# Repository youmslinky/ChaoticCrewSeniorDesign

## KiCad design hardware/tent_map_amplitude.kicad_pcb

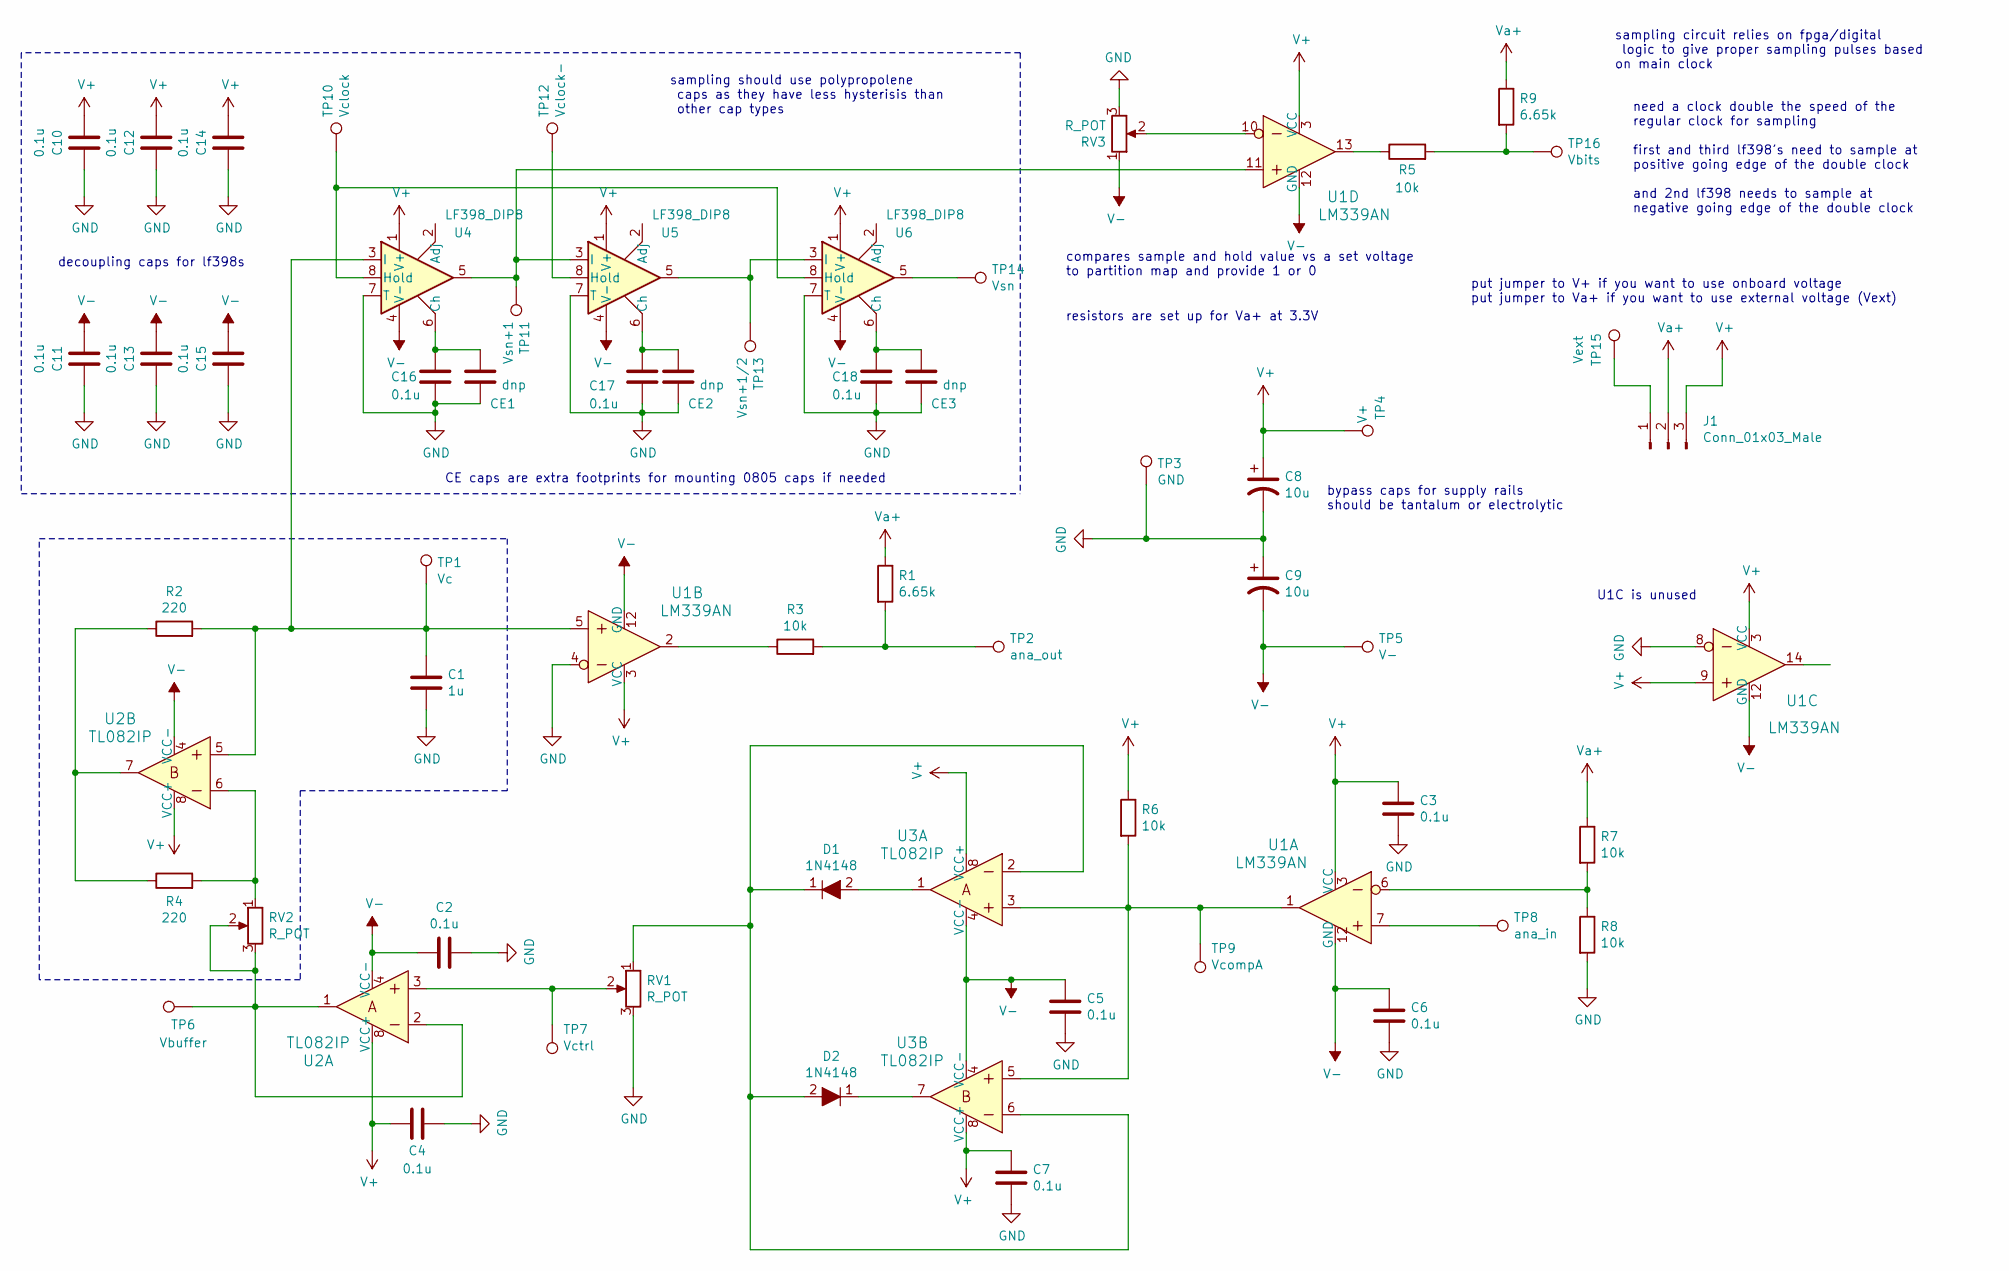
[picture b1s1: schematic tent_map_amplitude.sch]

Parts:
C1: 1u; C_0805_2012Metric_Pad1.18x1.45mm_HandSolder
C2, C3, C4, C5, C6, C7, C10, C11, C12, C13, C14, C15: 0.1u; C_0805_2012Metric_Pad1.18x1.45mm_HandSolder
C8, C9: 10u; CP_Radial_D5.0mm_P2.00mm
C16, C17, C18: 0.1u; C_Rect_L10.3mm_W5.0mm_P7.50mm_MKS4
CE1, CE2, CE3: dnp; C_0805_2012Metric_Pad1.18x1.45mm_HandSolder
D1, D2: 1N4148; Diode_DO-35_P10mm; MPN 1N4148; Digi-Key_PN 1N4148FS-ND
J1: Conn_01x03_Male; PinHeader_1x03_P2.54mm_Vertical
R1, R9: 6.65k; R_0805_2012Metric_Pad1.20x1.40mm_HandSolder
R2, R4: 220; R_0805_2012Metric_Pad1.20x1.40mm_HandSolder
R3, R5, R6, R7, R8: 10k; R_0805_2012Metric_Pad1.20x1.40mm_HandSolder
RV1, RV2, RV3: R_POT; Potentiometer_Bourns_3296W_Vertical
TP1: Vc; TestPoint_Bridge_Pitch2.54mm_Drill1.0mm
TP2: ana_out; TestPoint_Bridge_Pitch2.54mm_Drill1.0mm
TP3: GND; TestPoint_Bridge_Pitch2.54mm_Drill1.0mm
TP4: V+; TestPoint_Bridge_Pitch2.54mm_Drill1.0mm
TP5: V-; TestPoint_Bridge_Pitch2.54mm_Drill1.0mm
TP6: Vbuffer; TestPoint_Bridge_Pitch2.54mm_Drill1.0mm
TP7: Vctrl; TestPoint_Bridge_Pitch2.54mm_Drill1.0mm
TP8: ana_in; TestPoint_Bridge_Pitch2.54mm_Drill1.0mm
TP9: VcompA; TestPoint_Bridge_Pitch2.54mm_Drill1.0mm
TP10: Vclock; TestPoint_Bridge_Pitch2.54mm_Drill1.0mm
TP11: Vsn+1; TestPoint_Bridge_Pitch2.54mm_Drill1.0mm
TP12: Vclock-; TestPoint_Bridge_Pitch2.54mm_Drill1.0mm
TP13: Vsn+1/2; TestPoint_Bridge_Pitch2.54mm_Drill1.0mm
TP14: Vsn; TestPoint_Bridge_Pitch2.54mm_Drill1.0mm
TP15: Vext; TestPoint_Bridge_Pitch2.54mm_Drill1.0mm
TP16: Vbits; TestPoint_Bridge_Pitch2.54mm_Drill1.0mm
U1: LM339AN; DIP-14_W3mm; MPN LM339AN; Digi-Key_PN 296-6605-5-ND
U2, U3: TL082IP; DIP-8_W7.62mm; MPN TL082IP; Digi-Key_PN 296-1781-5-ND
U4, U5, U6: LF398_DIP8; DIP-8_W7.62mm

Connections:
GND: C1.2, C2.1, C3.2, C4.1, C5.2, C6.2, C7.2, C8.2, C9.1, C10.1, C11.1, C12.1, C13.1, C14.1, C15.1, C16.2, C17.2, C18.2, CE1.2, CE2.2, CE3.2, R8.2, RV1.3, RV3.3, TP3.1, U1.4, U1.8, U4.7 (T), U5.7 (T), U6.7 (T)
unnamed: C1.1, R2.2, TP1.1, U1.5, U2.5, U4.3 (I)
unnamed: C16.1, CE1.1, U4.6 (Ch)
unnamed: C17.1, CE2.1, U5.6 (Ch)
unnamed: C18.1, CE3.1, U6.6 (Ch)
unnamed: D1.1, D2.2, RV1.1, U3.2, U3.6
unnamed: D1.2, U3.1
unnamed: D2.1, U3.7
unnamed: J1.1, TP15.1
unnamed: R1.2, R3.2, TP2.1
unnamed: R2.1, R4.1, U2.7
unnamed: R3.1, U1.2
unnamed: R4.2, RV2.1, U2.6
unnamed: R5.1, U1.13
unnamed: R5.2, R9.2, TP16.1
unnamed: R6.2, TP9.1, U1.1, U3.3, U3.5
unnamed: R7.2, R8.1, U1.6
unnamed: RV1.2, TP7.1, U2.3
unnamed: RV2.2, RV2.3, TP6.1, U2.1, U2.2
unnamed: RV3.2, U1.10
unnamed: TP8.1, U1.7
unnamed: TP10.1, U4.8 (Hold), U6.8 (Hold)
unnamed: TP11.1, U1.11, U4.5, U5.3 (I)
unnamed: TP12.1, U5.8 (Hold)
unnamed: TP13.1, U5.5, U6.3 (I)
unnamed: TP14.1, U6.5
V+: C3.1, C4.2, C7.1, C8.1, C10.2, C12.2, C14.2, J1.3, R6.1, TP4.1, U1.3 (VCC), U1.9, U2.8 (VCC+), U3.8 (VCC+), U4.1 (V+), U5.1 (V+), U6.1 (V+)
V-: C2.2, C5.1, C6.1, C9.2, C11.2, C13.2, C15.2, RV3.1, TP5.1, U1.12 (GND), U2.4 (VCC-), U3.4 (VCC-), U4.4 (V-), U5.4 (V-), U6.4 (V-)
Va+: J1.2, R1.1, R7.1, R9.1

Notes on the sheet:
bypass caps for supply rails should be tantalum or electrolytic
sampling circuit relies on fpga/digital logic to give proper sampling pulses based on main clock
need a clock double the speed of the regular clock for sampling first and third lf398's need to sample at positive going edge of the double clock and 2nd lf398 needs to sample at negative going edge of the double clock
sampling should use polypropolene caps as they have less hysterisis than other cap types
decoupling caps for lf398s
CE caps are extra footprints for mounting 0805 caps if needed
U1C is unused
compares sample and hold value vs a set voltage to partition map and provide 1 or 0
put jumper to V+ if you want to use onboard voltage put jumper to Va+ if you want to use external voltage (Vext)
resistors are set up for Va+ at 3.3V

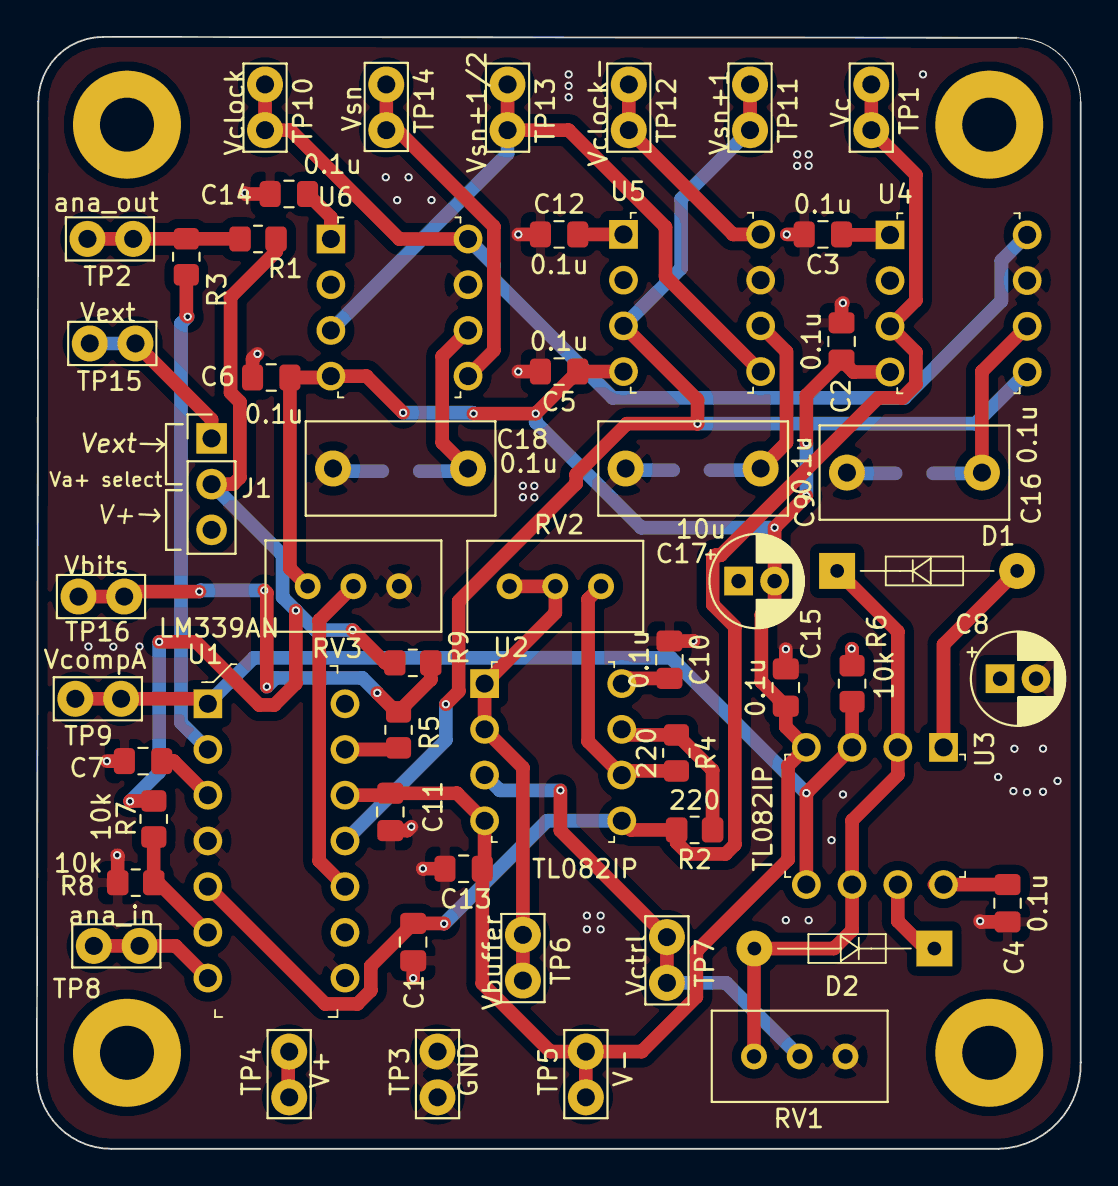
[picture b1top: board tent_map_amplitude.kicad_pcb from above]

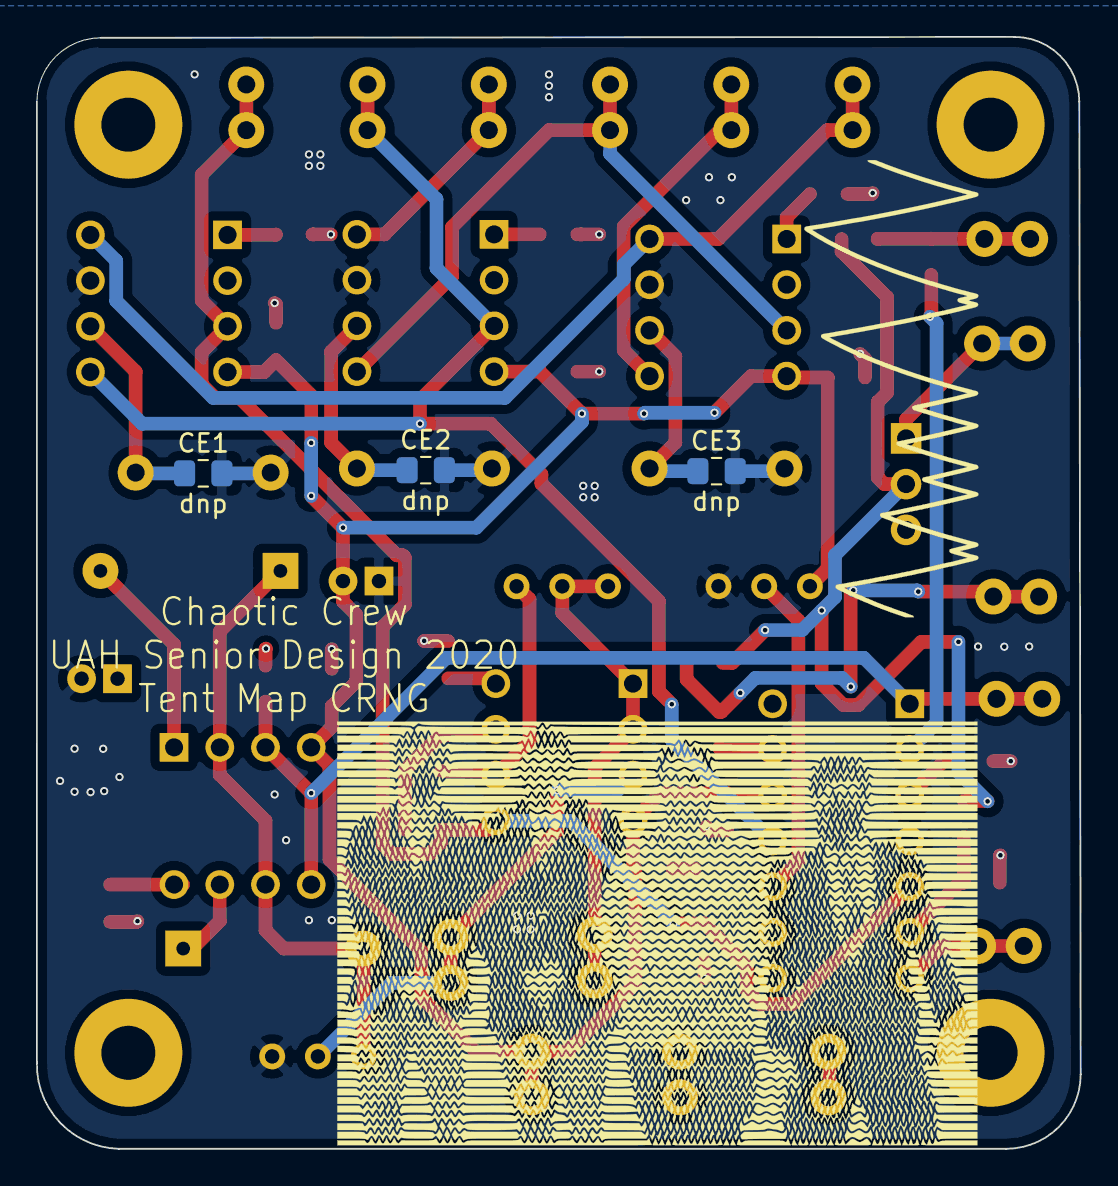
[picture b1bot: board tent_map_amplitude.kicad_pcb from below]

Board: 4 copper layers, 58.0 x 61.8 mm, 58 parts (3 on the bottom side), 29 nets.

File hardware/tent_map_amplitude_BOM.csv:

Reference, Quantity, Value, Footprint, Datasheet, Category, DK_Datasheet_Link, DK_Detail_Page, Description, Digi-Key_PN, Family, MPN, Manufacturer, Status
C1 ,1,"1u","Capacitor_SMD:C_0805_2012Metric_Pad1.18x1.45mm_HandSolder","~"
C16 C17 C18 ,3,"0.1u","Capacitor_THT:C_Rect_L10.3mm_W5.0mm_P7.50mm_MKS4","~"
C2 C3 C4 C5 C6 C7 C10 C11 C12 C13 C14 C15 ,12,"0.1u","Capacitor_SMD:C_0805_2012Metric_Pad1.18x1.45mm_HandSolder","~"
C8 C9 ,2,"10u","Capacitor_THT:CP_Radial_D5.0mm_P2.00mm","~"
D1 D2 ,2,"1N4148","digikey-footprints:Diode_DO-35_P10mm","https://www.onsemi.com/pub/Collateral/1N914-D.PDF","Discrete Semiconductor Products","https://www.onsemi.com/pub/Collateral/1N914-D.PDF","/product-detail/en/on-semiconductor/1N4148/1N4148FS-ND/458603","DIODE GEN PURP 100V 200MA DO35","1N4148FS-ND","Diodes - Rectifiers - Single","1N4148","ON Semiconductor","Active"
R2 R4 ,2,"220","Resistor_SMD:R_0805_2012Metric_Pad1.20x1.40mm_HandSolder","~"
R5 ,1,"2k","Resistor_SMD:R_0805_2012Metric_Pad1.20x1.40mm_HandSolder","~"
R1 R3 R6 R7 R8 ,5,"1k","Resistor_SMD:R_0805_2012Metric_Pad1.20x1.40mm_HandSolder","~"
RV1 ,1,"R_POT","Potentiometer_THT:Potentiometer_Bourns_3296W_Vertical","~"
TP1 ,1,"Vc","TestPoint:TestPoint_Bridge_Pitch2.54mm_Drill1.0mm","~"
TP10 ,1,"Vclock","TestPoint:TestPoint_Bridge_Pitch2.54mm_Drill1.0mm","~"
TP11 ,1,"Vsn+1","TestPoint:TestPoint_Bridge_Pitch2.54mm_Drill1.0mm","~"
TP12 ,1,"Vclock-","TestPoint:TestPoint_Bridge_Pitch2.54mm_Drill1.0mm","~"
TP13 ,1,"Vsn+1/2","TestPoint:TestPoint_Bridge_Pitch2.54mm_Drill1.0mm","~"
TP14 ,1,"Vsn","TestPoint:TestPoint_Bridge_Pitch2.54mm_Drill1.0mm","~"
TP15 ,1,"V+3.3","TestPoint:TestPoint_Bridge_Pitch2.54mm_Drill1.0mm","~"
TP2 ,1,"ana_out","TestPoint:TestPoint_Bridge_Pitch2.54mm_Drill1.0mm","~"
TP3 ,1,"GND","TestPoint:TestPoint_Bridge_Pitch2.54mm_Drill1.0mm","~"
TP4 ,1,"V+","TestPoint:TestPoint_Bridge_Pitch2.54mm_Drill1.0mm","~"
TP5 ,1,"V-","TestPoint:TestPoint_Bridge_Pitch2.54mm_Drill1.0mm","~"
TP6 ,1,"Vbuffer","TestPoint:TestPoint_Bridge_Pitch2.54mm_Drill1.0mm","~"
TP7 ,1,"Vctrl","TestPoint:TestPoint_Bridge_Pitch2.54mm_Drill1.0mm","~"
TP8 ,1,"ana_in","TestPoint:TestPoint_Bridge_Pitch2.54mm_Drill1.0mm","~"
TP9 ,1,"VcompA","TestPoint:TestPoint_Bridge_Pitch2.54mm_Drill1.0mm","~"
U1 ,1,"LM339AN","digikey-footprints:DIP-14_W3mm","http://www.ti.com/general/docs/suppproductinfo.tsp?distId=10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","Integrated Circuits (ICs)","http://www.ti.com/general/docs/suppproductinfo.tsp?distId=10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","/product-detail/en/texas-instruments/LM339AN/296-6605-5-ND/372806","IC QUAD DIFF COMPARATOR 14-DIP","296-6605-5-ND","Linear - Comparators","LM339AN","Texas Instruments","Active"
U2 U3 ,2,"TL082IP","digikey-footprints:DIP-8_W7.62mm","http://www.ti.com/general/docs/suppproductinfo.tsp?distId=10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","Integrated Circuits (ICs)","http://www.ti.com/general/docs/suppproductinfo.tsp?distId=10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","/product-detail/en/texas-instruments/TL082IP/296-1781-5-ND/277426","IC OPAMP JFET 2 CIRCUIT 8DIP","296-1781-5-ND","Linear - Amplifiers - Instrumentation, OP Amps, Buffer Amps","TL082IP","Texas Instruments","Active"
U4 U5 U6 ,3,"LF398_DIP8","digikey-footprints:DIP-8_W7.62mm","http://www.ti.com/lit/ds/symlink/lf398-n.pdf"

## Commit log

2020-10-09 Add matlab ltspice tent map statistic tests
2020-10-09 Minor changes
2020-10-09 Add existing python files
2020-10-09 Add brief descriptions of scripts
2020-10-13 Add code to put labels at same angle as lines
2020-10-13 add 2 methods to partition map to get bit stream
2020-10-13 don't plot x=y line, because it doesn't fit our data
2020-10-13 p should be p1, because there is a p2
2020-10-17 Format py files with black
2020-10-22 Add comment about how input data needs to be arranged
2020-10-22 Give sampling code more descriptive variable names
2020-10-22 remove debug print
2020-10-22 Add kicad gitignore files
2020-10-22 Format conditions for sampling better
2020-10-22 Add initial kicad files
2020-10-22 Add some tent map plots
2020-10-22 Add circuit rev3 images from ltspice
2020-10-22 Add basic circuit schematic
2020-10-22 Add decoupling capacitors
2020-10-22 Remove extra capacitors, only need 2 for each IC package
2020-10-22 variable resistor out of super diodes should be connected to ground, not V-
2020-10-22 Use correct lm339AN part, auto-label components
2020-10-22 Assign temporary footprints, need to verify based on selection of components
2020-10-22 Add template project for oshpark 4 layer board
2020-10-22 Add test points, add WIP lf398 sample and hold circuit
2020-10-22 Add tons of plots
2020-10-22 Add file picker for matlab stats test
2020-10-22 Add beal circuits (edited some by jdk)
2020-10-22 Update gitignore for ltspice
2020-10-23 Complete PCB (unreviewed)
2020-10-23 Add gerbers for first board rev
2020-10-23 Reroute trace
2020-10-23 Add existing BOM
2020-10-23 Add BOM
2020-10-23 update pcb and schematic to have 3.3V input for interfacing with DE-10 nano
2020-10-25 use 3.3v for logic level for input comparator
2020-10-25 Go back to old board design with all components on front, Merge previous changes
2020-10-26 Remove some uneeded traces and vias
2020-10-26 Add dip machine pin sockets 3d models
2020-10-26 Move big cap, route trace through legs of dip package
2020-10-26 Add variable resistor 2
2020-10-27 Make changes based on beal's recomendations, add extra caps on schematic for extra 0805 footprint, add unused comparator symbols
2020-10-27 Add extra cap footprints, change trace tolerance to 10thou, Add second variable resistor
2020-10-27 Add 3.5mm mounting holes
2020-10-27 Move traces off of ground and power planes
2020-10-27 Add stitching vias to fill in ground planes on top and bottom copper
2020-10-27 Add rounded board edges, move edges out to strengthen holes
2020-10-27 Fix board edge?
2020-10-27 Make board edges bigger, fix silk screens
2020-10-27 Change M3.5 to M3 mounting holes
2020-10-27 Update gerbers to latest board
2020-10-27 Refill board (oops)
2020-10-27 Add libraries used to libs directory, fix library paths
2020-10-28 Add footprints used from digikey library
2020-10-29 Add art library folder
2020-10-29 Use extra comparator for sampled bitstream output
2020-10-29 Change output resistors so comparators can pull voltage all the way to ground
2020-10-29 Update PCB with previous commit changes
2020-10-30 Change resistors back, change resistors to properly do 0v to 3.3v output, add power switch jumper, change references to 3.3v to Va+
2020-10-30 Export gerbers gerbers for pcb V4
2020-11-18 Plot and save both waveform and tent map with slopes, use ground signal too
2020-11-18 Add misc. python files
2020-11-18 Add PCB 3d renders
